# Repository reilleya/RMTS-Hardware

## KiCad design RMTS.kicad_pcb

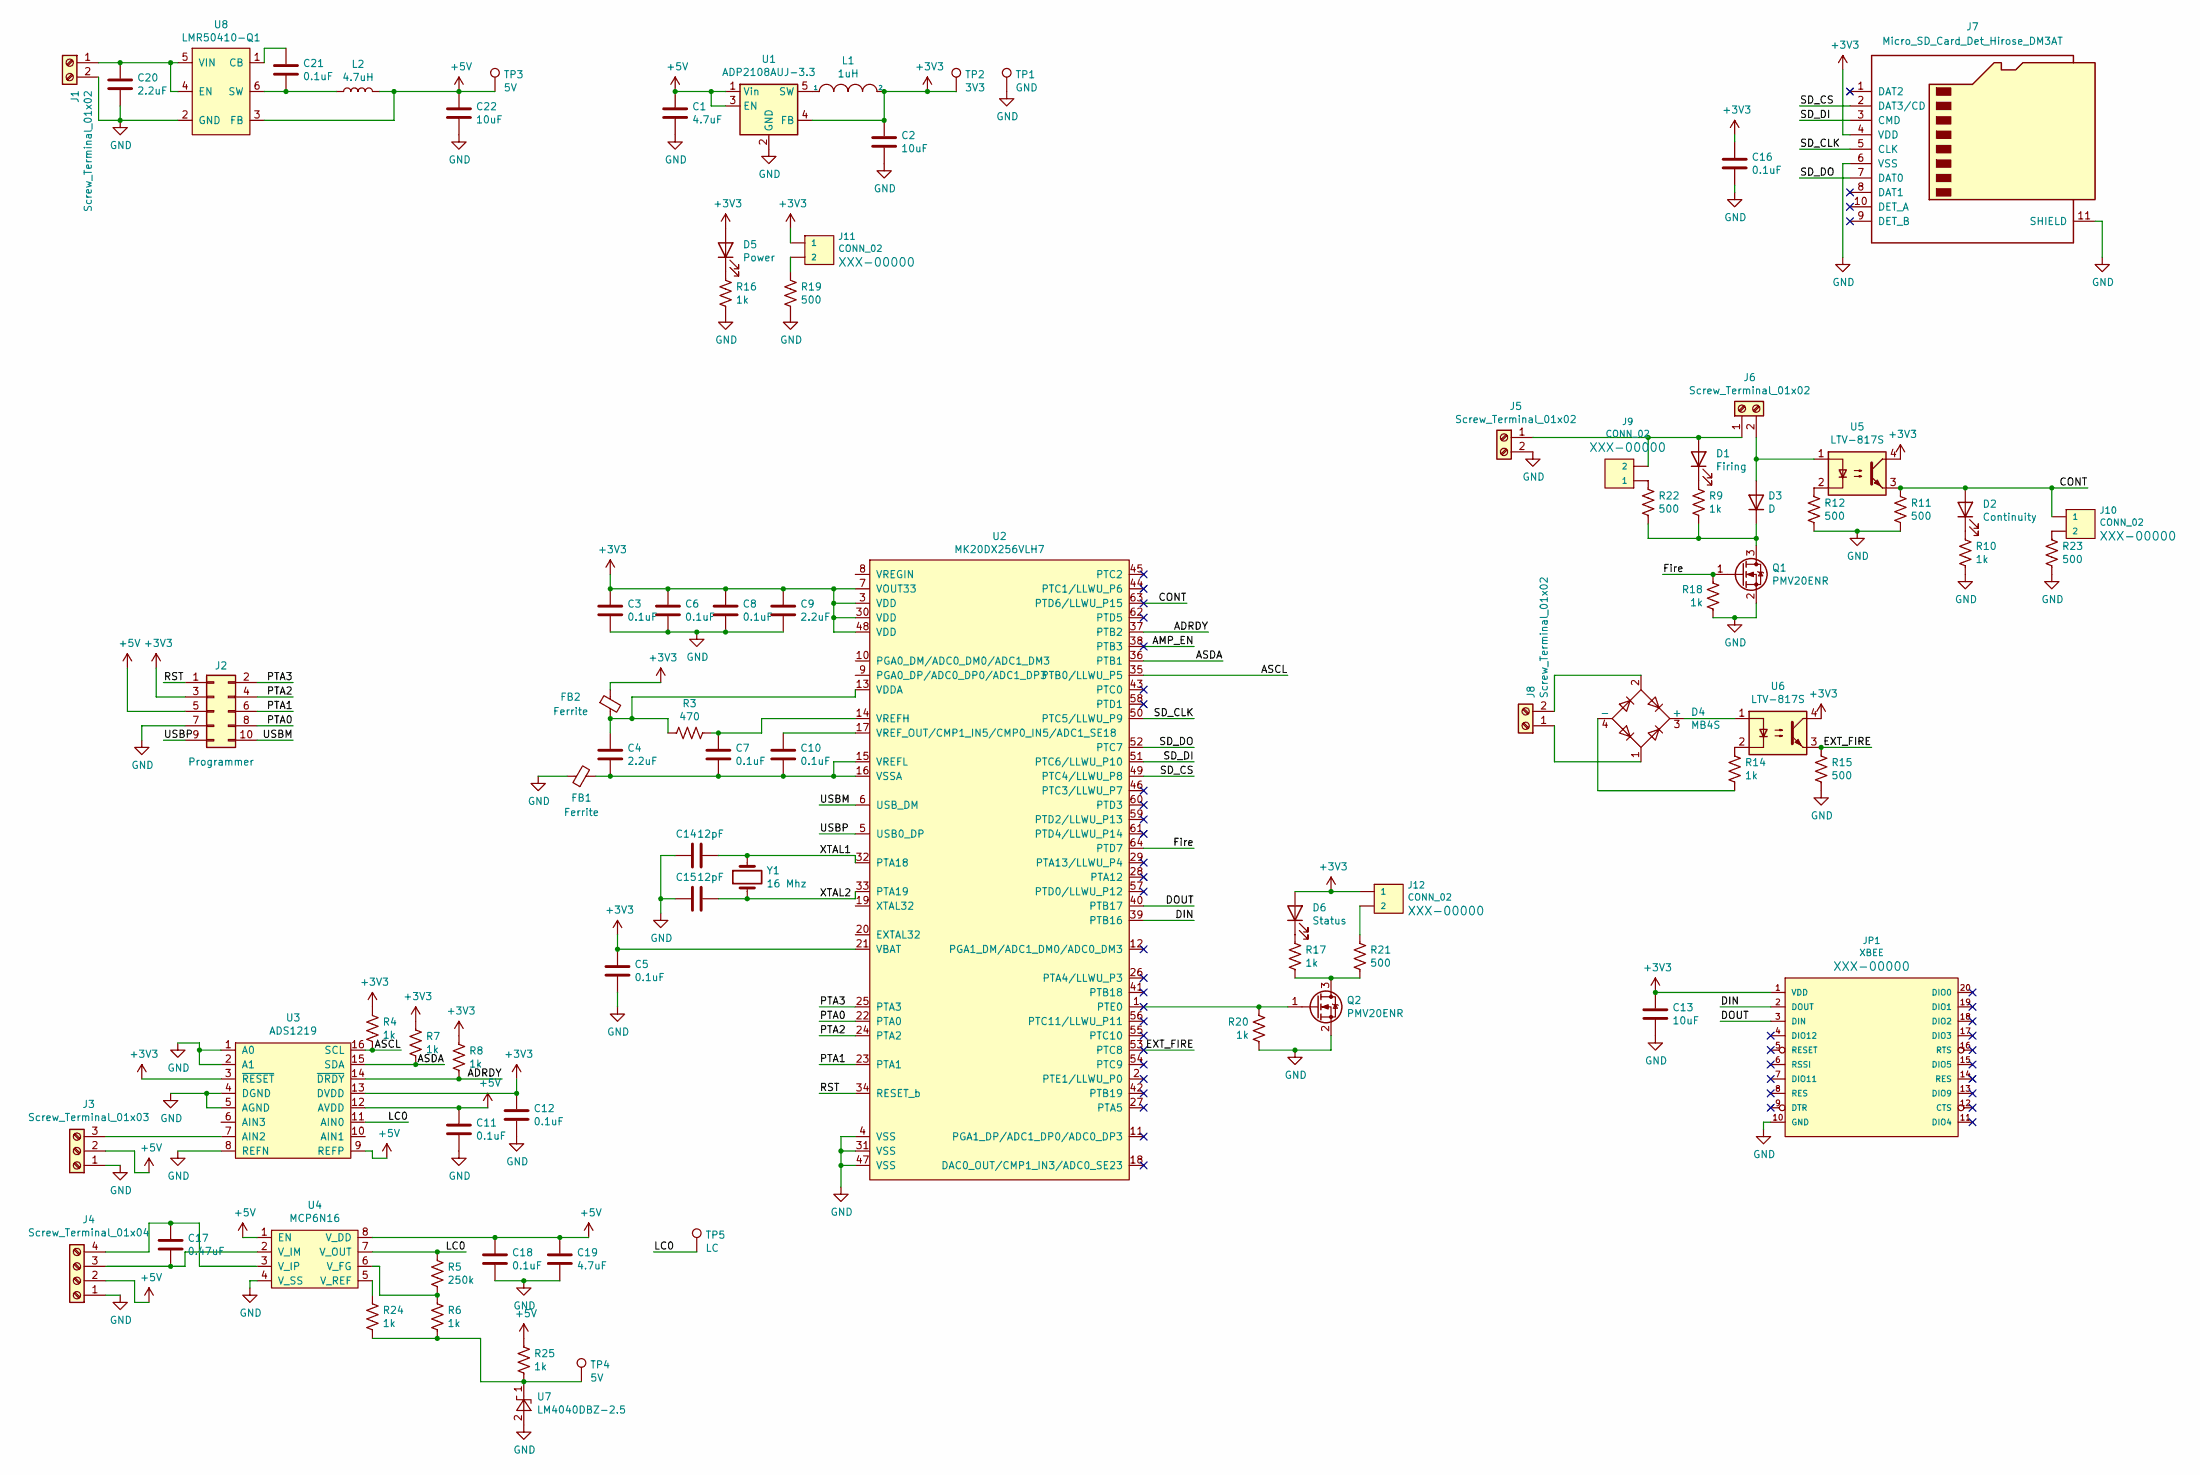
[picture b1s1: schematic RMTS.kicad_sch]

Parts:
C1, C19: 4.7uF; C_0805_2012Metric_Pad1.15x1.40mm_HandSolder; LCSC C1779
C2: 10uF; CP_Elec_5x3.9; LCSC C340737
C3, C5, C6, C7, C8, C10, C11, C12, C16, C18, C21: 0.1uF; C_0805_2012Metric_Pad1.15x1.40mm_HandSolder; LCSC C49678
C4, C9, C20: 2.2uF; C_0805_2012Metric_Pad1.15x1.40mm_HandSolder; LCSC C125847
C13, C22: 10uF; C_0805_2012Metric_Pad1.15x1.40mm_HandSolder; LCSC C15850
C14, C15: 12pF; C_0805_2012Metric_Pad1.15x1.40mm_HandSolder; LCSC C1792
C17: 0.47uF; C_0805_2012Metric_Pad1.15x1.40mm_HandSolder; LCSC C13967
D1: Firing; LED_0805_2012Metric_Pad1.15x1.40mm_HandSolder; LCSC C84256
D2: Continuity; LED_0805_2012Metric_Pad1.15x1.40mm_HandSolder; LCSC C84256
D3: D; D_SOD-128; LCSC C552950
D4: MB4S; TO-269AA; LCSC C151727
D5: Power; LED_0805_2012Metric_Pad1.15x1.40mm_HandSolder; LCSC C84256
D6: Status; LED_0805_2012Metric_Pad1.15x1.40mm_HandSolder; LCSC C84256
FB1, FB2: Ferrite; C_0805_2012Metric_Pad1.15x1.40mm_HandSolder; LCSC C97001
J1, J5, J6, J8: Screw_Terminal_01x02; SCREWTERMINAL-3.5MM-2
J2: Programmer; PinHeader_2x05_P2.00mm_Vertical
J3: Screw_Terminal_01x03; SCREWTERMINAL-3.5MM-3
J4: Screw_Terminal_01x04; SCREWTERMINAL-3.5MM-4
J7: Micro_SD_Card_Det_Hirose_DM3AT; microSD_HC_Hirose_DM3AT-SF-PEJM5
J9, J10, J11, J12: CONN_02; 1X02
JP1: XBEE
L1: 1uH; L_0805_2012Metric_Pad1.15x1.40mm_HandSolder; LCSC C1042
L2: 4.7uH; L_0805_2012Metric_Pad1.15x1.40mm_HandSolder; LCSC C86090
Q1, Q2: PMV20ENR; SOT-23; LCSC C456088
R3: 470; R_0805_2012Metric_Pad1.15x1.40mm_HandSolder; LCSC C17710
R4, R6, R7, R8, R9, R10, R14, R16, R17, R18, R20, R24, R25: 1k; R_0805_2012Metric_Pad1.15x1.40mm_HandSolder; LCSC C17513
R5: 250k; R_0805_2012Metric_Pad1.15x1.40mm_HandSolder; LCSC C25825
R11, R12, R15, R19, R22, R23: 500; R_0805_2012Metric_Pad1.15x1.40mm_HandSolder; LCSC C17734
R21: 500; R_0805_2012Metric_Pad1.15x1.40mm_HandSolder; LCSC C17513
TP1: GND; TestPoint_THTPad_2.0x2.0mm_Drill1.0mm
TP2: 3V3; TestPoint_THTPad_2.0x2.0mm_Drill1.0mm
TP3, TP4: 5V; TestPoint_THTPad_2.0x2.0mm_Drill1.0mm
TP5: LC; TestPoint_THTPad_2.0x2.0mm_Drill1.0mm
U1: ADP2108AUJ-3.3; TSOT-23-5; LCSC C143875
U2: MK20DX256VLH7; LQFP-64_10x10mm_P0.5mm; LCSC C511780
U3: ADS1219; TSSOP-16_4.4x5mm_P0.65mm; LCSC C2869313
U4: MCP6N16; MSOP-8_3x3mm_P0.65mm; LCSC C636381
U5, U6: LTV-817S; SMDIP-4_W9.53mm; LCSC C189217
U7: LM4040DBZ-2.5; SOT-23; LCSC C468180
U8: LMR50410-Q1; SOT-23-6; LCSC C2871822
Y1: 16 Mhz; HC-49S-SMD-2P-Mini; LCSC C2975359

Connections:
+3V3: C2.1, C3.1, C5.1, C6.1, C8.1, C9.1, C12.1, C13.1, C16.1, D5.2 (A), D6.2 (A), FB2.1, J2.3, J7.4 (VDD), J11.1, J12.1, JP1.1 (VDD), L1.2, R4.1, R7.1, R8.1, TP2.1, U1.4 (FB), U2.3 (VDD), U2.7 (VOUT33), U2.21 (VBAT), U2.30 (VDD), U2.48 (VDD), U3.3 (~RESET), U3.13 (DVDD), U5.4, U6.4
+5V: C1.1, C11.1, C18.1, C19.1, C22.1, J2.5, J3.2, J4.2, L2.2, R25.1, TP3.1, U1.1 (Vin), U1.3 (EN), U3.9 (REFP), U3.12 (AVDD), U4.1 (EN), U4.8 (V_DD), U8.3 (FB)
/ADRDY: R8.2, U2.37 (PTB2), U3.14 (~DRDY)
/AMP_EN: U2.38 (PTB3)
/ASCL: R4.2, U2.35 (PTB0/LLWU_P5), U3.16 (SCL)
/ASDA: R7.2, U2.36 (PTB1), U3.15 (SDA)
/CONT: D2.2 (A), J10.1, R11.1, U2.63 (PTD6/LLWU_P15), U5.3
/DIN: JP1.2 (DOUT), U2.39 (PTB16)
/DOUT: JP1.3 (DIN), U2.40 (PTB17)
/EXT_FIRE: R15.1, U2.53 (PTC8), U6.3
/Fire: Q1.1 (G), R18.1, U2.64 (PTD7)
/LC0: R5.1, TP5.1, U3.11 (AIN0), U4.7 (V_OUT)
/PTA0: J2.8, U2.22 (PTA0)
/PTA1: J2.6, U2.23 (PTA1)
/PTA2: J2.4, U2.24 (PTA2)
/PTA3: J2.2, U2.25 (PTA3)
/RST: J2.1, U2.34 (RESET_b)
/SD_CLK: J7.5 (CLK), U2.50 (PTC5/LLWU_P9)
/SD_CS: J7.2 (DAT3/CD), U2.49 (PTC4/LLWU_P8)
/SD_DI: J7.3 (CMD), U2.51 (PTC6/LLWU_P10)
/SD_DO: J7.7 (DAT0), U2.52 (PTC7)
/USBM: J2.10, U2.6 (USB_DM)
/USBP: J2.9, U2.5 (USB0_DP)
/XTAL1: C14.1, U2.32 (PTA18), Y1.1
/XTAL2: C15.1, U2.33 (PTA19), Y1.2
GND: C1.2, C2.2, C3.2, C5.2, C6.2, C8.2, C9.2, C11.2, C12.2, C13.2, C14.2, C15.2, C16.2, C18.2, C19.2, C20.2, C22.2, FB1.1, J1.2, J2.7, J3.1, J4.1, J5.2, J7.6 (VSS), J7.11 (SHIELD), JP1.10 (GND), Q1.2 (S), Q2.2 (S), R10.2, R11.2, R12.2, R15.2, R16.2, R18.2, R19.2, R20.2, R23.2, TP1.1, U1.2 (GND), U2.4 (VSS), U2.31 (VSS), U2.47 (VSS), U3.1 (A0), U3.2 (A1), U3.4 (DGND), U3.5 (AGND), U3.8 (REFN), U4.4 (V_SS), U7.2 (A), U8.2 (GND)
unnamed: D1.2 (A), J5.1, J6.1, J9.2
unnamed: D1.1 (K), R9.1
unnamed: D2.1 (K), R10.1
unnamed: D3.2 (A), J6.2, U5.1
unnamed: D3.1 (K), Q1.3 (D), R9.2, R22.2
unnamed: D4.3 (+), U6.1
unnamed: D4.4 (-), R14.2
unnamed: D5.1 (K), R16.1
unnamed: D6.1 (K), R17.1
unnamed: C20.1, J1.1, U8.4 (EN), U8.5 (VIN)
unnamed: J3.3, U3.7 (AIN2)
unnamed: C17.2, J4.3, U4.2 (V_IM)
unnamed: C17.1, J4.4, U4.3 (V_IP)
unnamed: D4.1, J8.1
unnamed: D4.2, J8.2
unnamed: J9.1, R22.1
unnamed: J10.2, R23.1
unnamed: J11.2, R19.1
unnamed: J12.2, R21.1
unnamed: Q2.3 (D), R17.2, R21.2
unnamed: R12.1, U5.2
unnamed: R14.1, U6.2
unnamed: L1.1, U1.5 (SW)
unnamed: C4.1, FB2.2, R3.2, U2.13 (VDDA)
unnamed: C7.1, R3.1, U2.14 (VREFH)
unnamed: C4.2, C7.2, C10.2, FB1.2, U2.15 (VREFL), U2.16 (VSSA)
unnamed: C10.1, U2.17 (VREF_OUT/CMP1_IN5/CMP0_IN5/ADC1_SE18)
unnamed: R5.2, R6.1, U4.6 (V_FG)
unnamed: R24.1, U4.5 (V_REF)
unnamed: R6.2, R24.2, R25.2, TP4.1, U7.1 (K)
unnamed: C21.1, U8.1 (CB)
unnamed: C21.2, L2.1, U8.6 (SW)

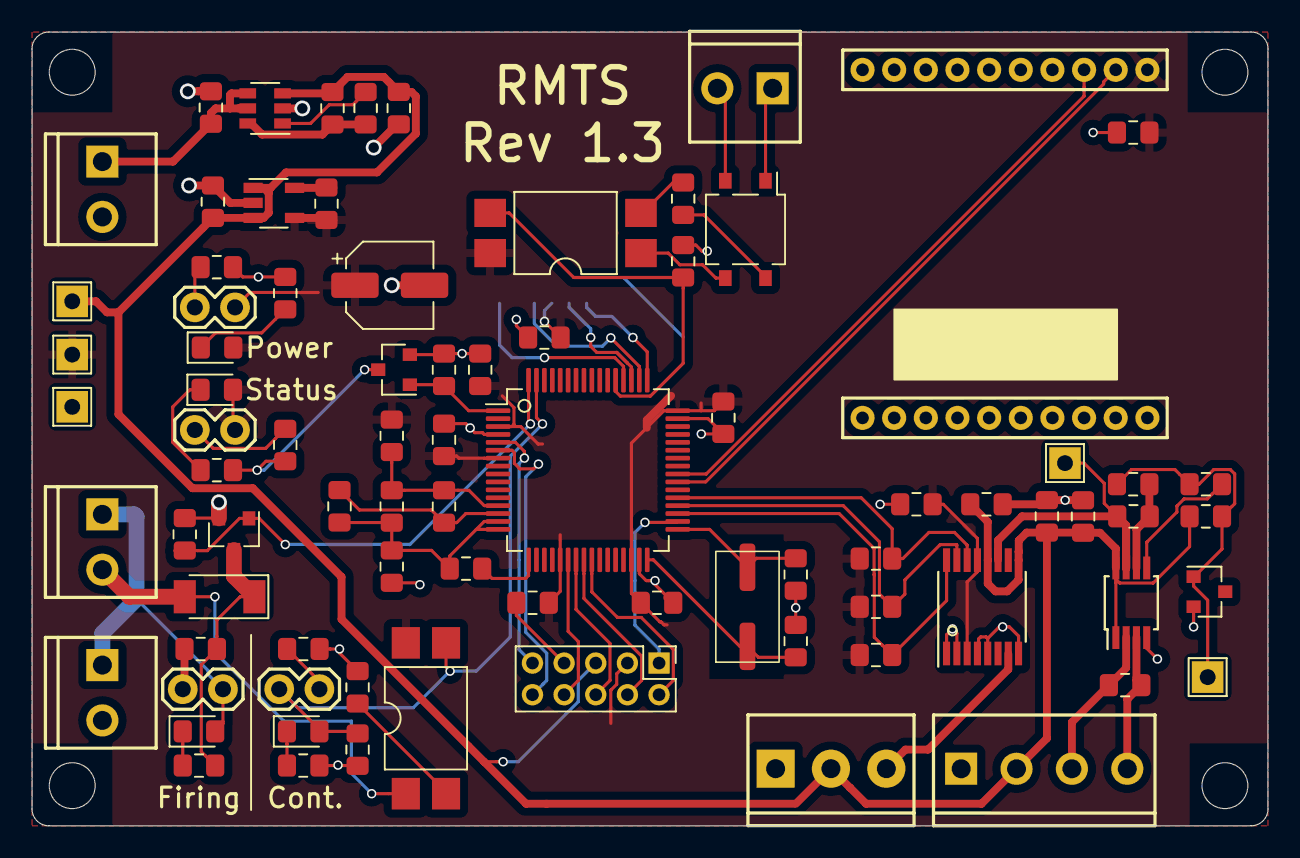
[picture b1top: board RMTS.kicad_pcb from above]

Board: 2 copper layers, 78.1 x 50.2 mm, 83 parts (1 on the bottom side), 57 nets.

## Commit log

2019-07-29 Initial commit with schematic
2019-08-02 Updated schematic, started layout
2019-08-03 Added load capacitors to crystal
2019-08-03 Fixed unit notation
2019-08-03 Added backup crystal schematic symbol
2019-08-03 Updated SD card connector to standard
2019-08-03 Removed previous SD card connector
2019-08-03 Added no-connect flags
2019-08-03 Fixed rescued symbols
2019-08-03 Fixed broken header
2019-08-03 Fixed older microSD footprint
2019-08-10 Finished layout
2019-08-11 Cleaned up silkscreen
2019-08-11 Added label to screw terminals
2019-08-11 Added 3v3 top plane
2019-08-24 Changed USB to full size, connected amp enable, cleaned up routing
2019-08-25 Fixed mistakes
2019-08-25 Added keepout regions near mounting holes
2019-09-08 Pulled ADC enable high, added diode to firing circuit, rerouted some traces
2019-09-15 Removed backup crystal, resized board
2019-10-07 Added continuity optocoupler, capacitor pads to loadcell connection
2020-02-08 Added resistor to avoid battery shutting off
2020-02-12 Removed USB pyro power jumper
2020-02-25 Updated amplifier to MCP6N16, incremented revision number
2020-03-05 Flipped SD card, added external firing circuit
2020-03-06 Added power LED, moved labels, cleaned up some traces
2020-03-10 Added status LED, hid labels
2020-03-12 Added headers for LEDs, aligned some components better
2020-03-28 Added logo
2020-03-29 Added silkscreen box for serial number
2020-04-12 Increased font size of terminal block labels
2020-04-20 Updated logo to bitmap
2020-05-23 Add pulldown to firing circuit
2020-06-29 Add LCSC part numbers to components
2020-09-17 Made external LED channels separate from onboard LEDs
2020-09-22 Decrease keepalive resistor value
2020-09-29 Increase resistance of trigger circuit
2020-12-27 Improve amplifier circuit
2021-01-17 Update programmer header, remove USB port
2021-01-18 Added 5v reg, broke layout
2021-01-21 Fixed layout of new 5v regulator
2021-01-24 Upgrade firing diode
2021-01-24 Added test points
2021-01-30 Adjust silkscreen
2021-01-30 Get 5v from programmer
2021-02-07 Cleanup
2021-02-20 Fix 5v regulator
2021-02-23 Fix status LED
2021-03-13 Swap out diode footprint
2021-03-22 Update LCSC
2024-07-10 Update to KiCad 8
2025-01-09 Have JLC populate more components
